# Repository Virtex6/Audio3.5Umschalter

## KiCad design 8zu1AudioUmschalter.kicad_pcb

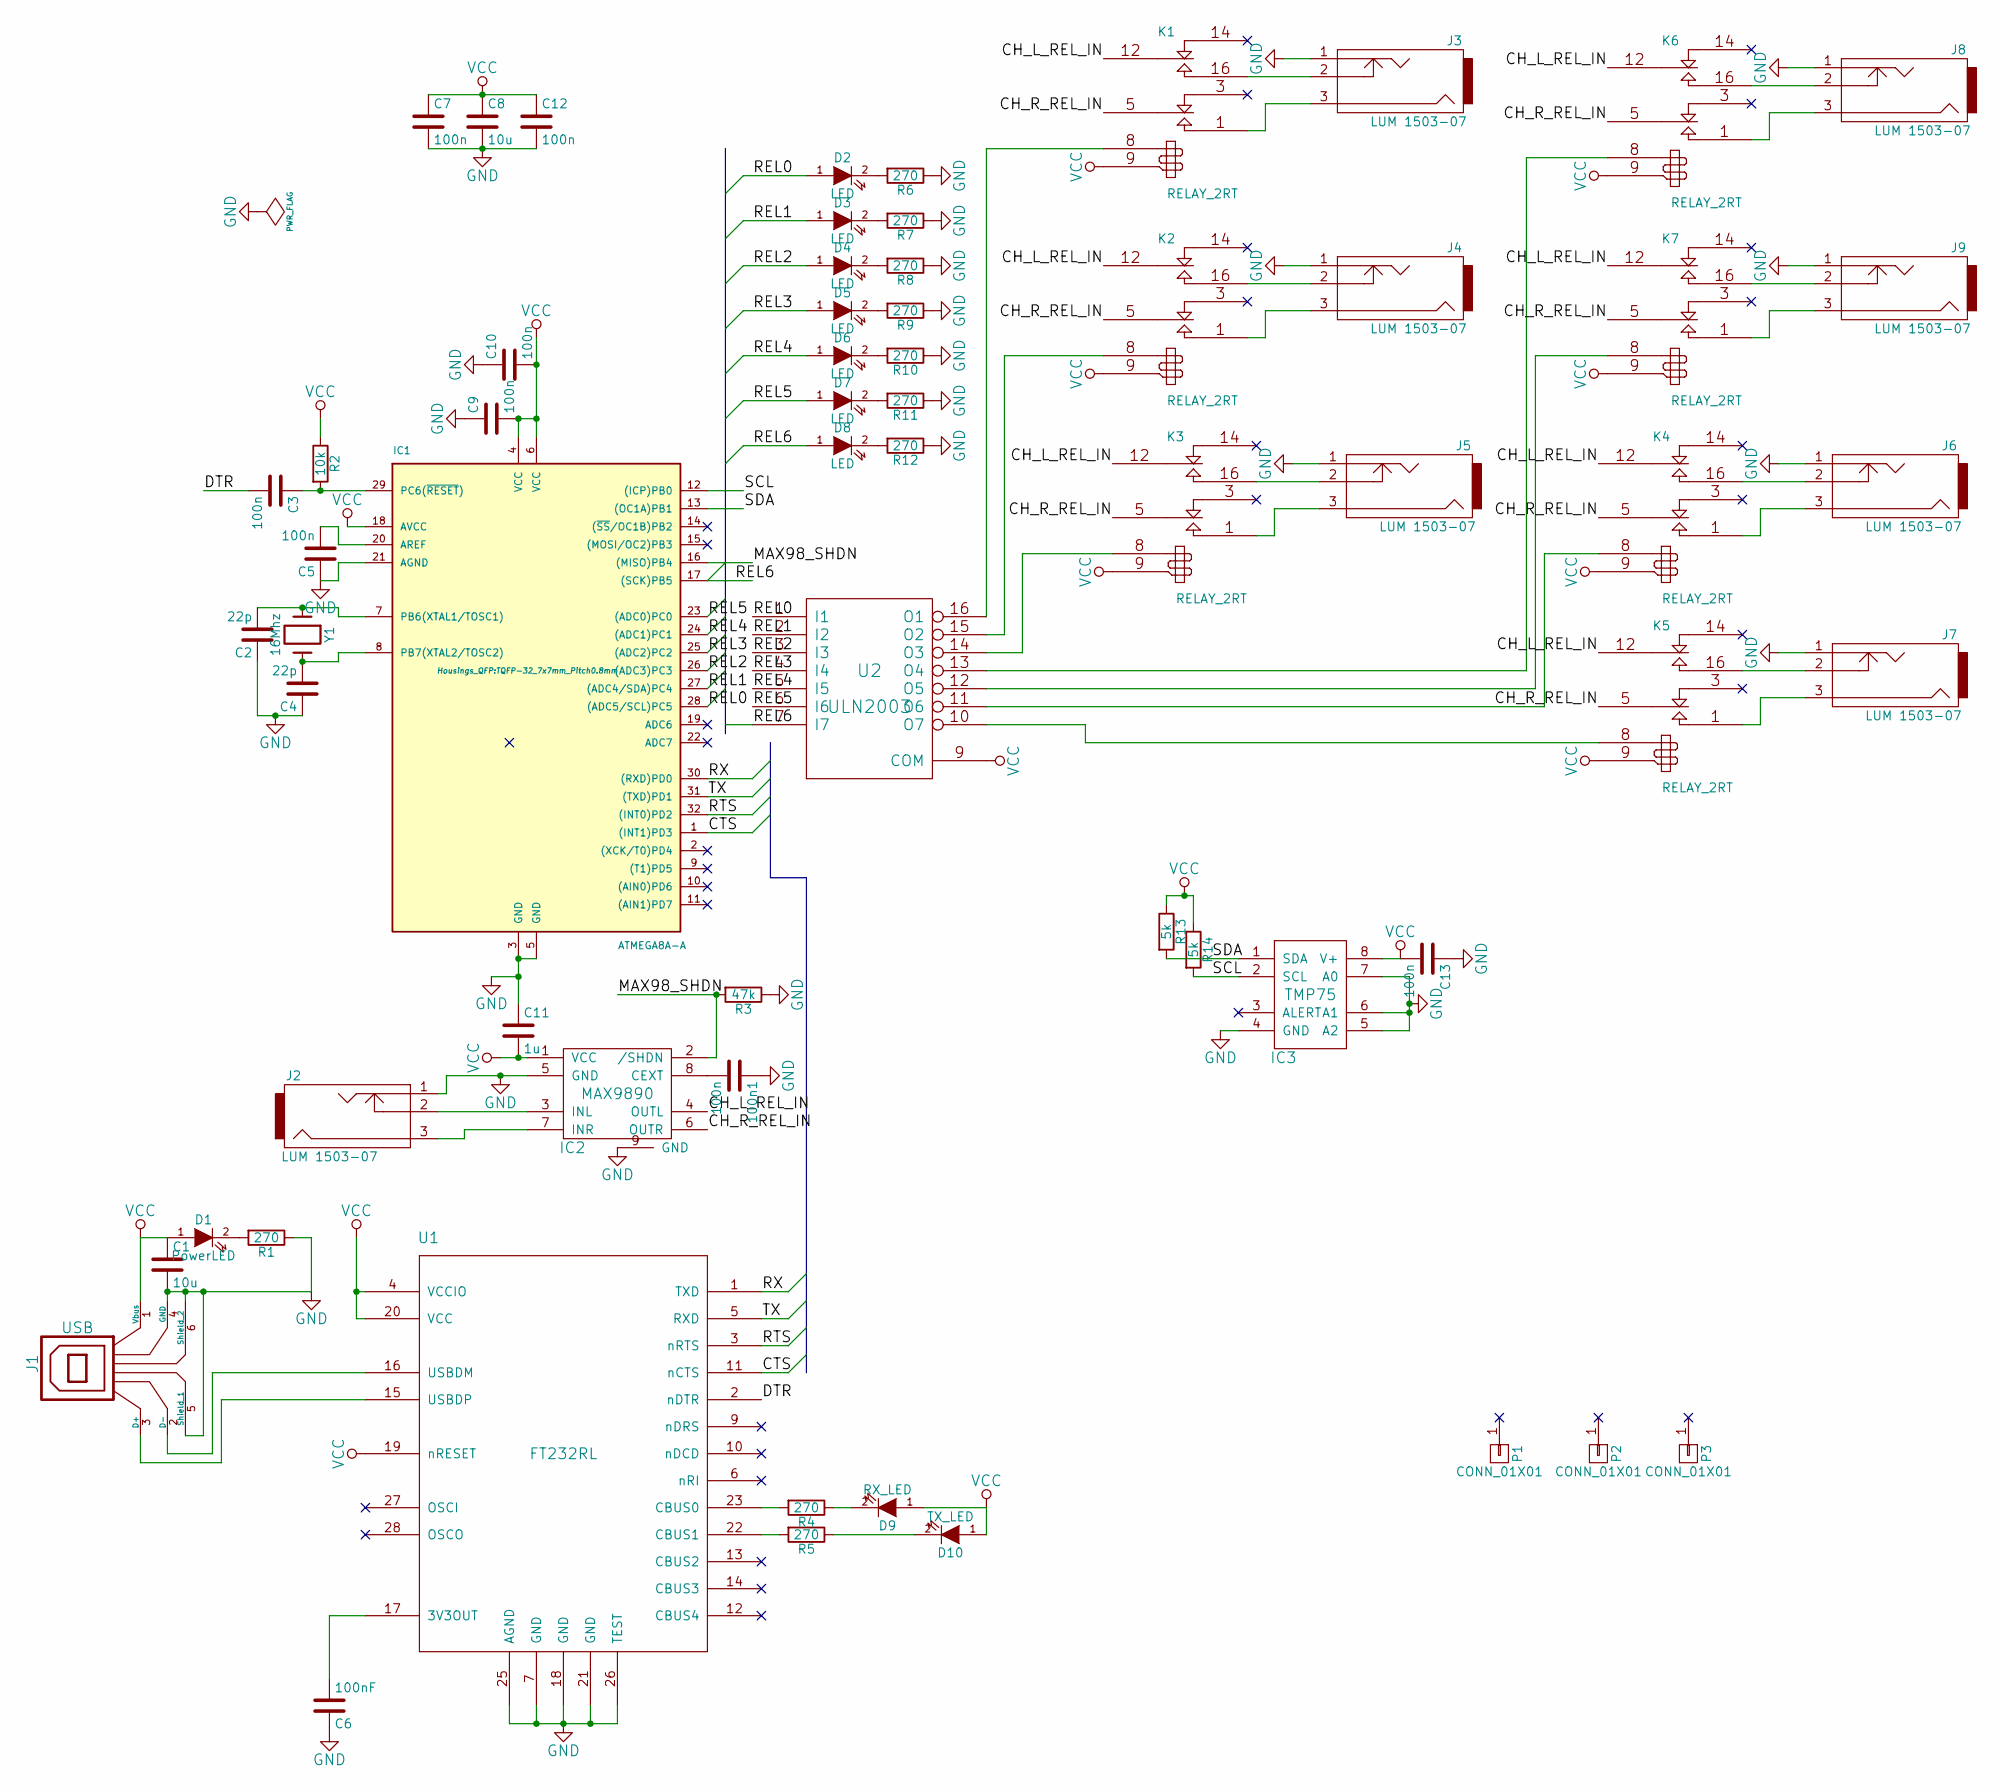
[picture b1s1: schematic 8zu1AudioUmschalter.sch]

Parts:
100n1: 100n; C_0603
C1, C8: 10u; C_0805
C2, C4: 22p; C_0603
C3, C5, C7, C9, C10, C12, C13: 100n; C_0603
C6: 100nF; C_0603
C11: 1u; C_0603
D1: PowerLED; LED-0603
D2, D3, D4, D5, D6, D7, D8: LED; LED-0603
D9: RX_LED; LED-0603
D10: TX_LED; LED-0603
IC1: ATMEGA8A-A; TQFP-32_7x7mm_Pitch0.8mm
IC2: MAX9890; DFN-8-1EP_3x3mm_Pitch0.65mm
IC3: TMP75; SOIC-8-N
J1: USB; USB_Mini-B
J2, J3, J4, J5, J6, J7, J8, J9: LUM 1503-07; LUM1503
K1, K2, K3, K4, K5, K6, K7: RELAY_2RT; REL_NA05W
P1, P2, P3: CONN_01X01; MountingHole_3mm
R1, R4, R5, R6, R7, R8, R9, R10, R11, R12: 270; R_0603
R2: 10k; R_0603
R3: 47k; R_0603
R13, R14: 5k; R_0603
U1: FT232RL; SSOP-28_5.3x10.2mm_Pitch0.65mm
U2: ULN2003; SO-16-N
Y1: 16Mhz; Crystal_HC49-U_Vertical

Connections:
/CH_L_REL_IN: IC2.4 (OUTL), K1.12 (C2), K2.12 (C2), K3.12 (C2), K4.12 (C2), K5.12 (C2), K6.12 (C2), K7.12 (C2)
/CH_R_REL_IN: IC2.6 (OUTR), K1.5 (C1), K2.5 (C1), K3.5 (C1), K4.5 (C1), K5.5 (C1), K6.5 (C1), K7.5 (C1)
/CTS: IC1.1 ((INT1)PD3), U1.11 (nCTS)
/DTR: C3.2, U1.2 (nDTR)
/MAX98_SHDN: IC1.16 ((MISO)PB4), IC2.2 (/SHDN), R3.2
/REL0: D2.1 (A), IC1.28 ((ADC5/SCL)PC5), U2.1 (I1)
/REL1: D3.1 (A), IC1.27 ((ADC4/SDA)PC4), U2.2 (I2)
/REL2: D4.1 (A), IC1.26 ((ADC3)PC3), U2.3 (I3)
/REL3: D5.1 (A), IC1.25 ((ADC2)PC2), U2.4 (I4)
/REL4: D6.1 (A), IC1.24 ((ADC1)PC1), U2.5 (I5)
/REL5: D7.1 (A), IC1.23 ((ADC0)PC0), U2.6 (I6)
/REL6: D8.1 (A), IC1.17 ((SCK)PB5), U2.7 (I7)
/RTS: IC1.32 ((INT0)PD2), U1.3 (nRTS)
/RX: IC1.30 ((RXD)PD0), U1.1 (TXD)
/SCL: IC1.12 ((ICP)PB0), IC3.2 (SCL), R14.2
/SDA: IC1.13 ((OC1A)PB1), IC3.1 (SDA), R13.2
/TX: IC1.31 ((TXD)PD1), U1.5 (RXD)
GND: 100n1.1, C1.2, C2.1, C4.1, C5.1, C6.1, C7.2, C8.2, C9.1, C10.1, C11.1, C12.2, C13.1, IC1.3 (GND), IC1.5 (GND), IC1.21 (AGND), IC2.5 (GND), IC2.9 (GND), IC3.4 (GND), IC3.5 (A2), IC3.6 (A1), IC3.7 (A0), J1.4 (GND), J1.5 (Shield_1), J1.6 (Shield_2), J2.1, J3.1, J4.1, J5.1, J6.1, J7.1, J8.1, J9.1, R1.1, R3.1, R6.1, R7.1, R8.1, R9.1, R10.1, R11.1, R12.1, U1.7 (GND), U1.18 (GND), U1.21 (GND), U1.25 (AGND), U1.26 (TEST), U2.8 (GND)
unnamed: 100n1.2, IC2.8 (CEXT)
unnamed: C2.2, IC1.7 (PB6(XTAL1/TOSC1)), Y1.1
unnamed: C3.1, IC1.29 (PC6(~RESET~)), R2.2
unnamed: C4.2, IC1.8 (PB7(XTAL2/TOSC2)), Y1.2
unnamed: C5.2, IC1.20 (AREF)
unnamed: C6.2, U1.17 (3V3OUT)
unnamed: D1.2 (K), R1.2
unnamed: D2.2 (K), R6.2
unnamed: D3.2 (K), R7.2
unnamed: D4.2 (K), R8.2
unnamed: D5.2 (K), R9.2
unnamed: D6.2 (K), R10.2
unnamed: D7.2 (K), R11.2
unnamed: D8.2 (K), R12.2
unnamed: D9.2 (K), R4.1
unnamed: D10.2 (K), R5.1
unnamed: IC2.3 (INL), J2.2
unnamed: IC2.7 (INR), J2.3
unnamed: J1.2 (D-), U1.16 (USBDM)
unnamed: J1.3 (D+), U1.15 (USBDP)
unnamed: J3.2, K1.16 (T2)
unnamed: J3.3, K1.1 (T1)
unnamed: J4.2, K2.16 (T2)
unnamed: J4.3, K2.1 (T1)
unnamed: J5.2, K3.16 (T2)
unnamed: J5.3, K3.1 (T1)
unnamed: J6.2, K4.16 (T2)
unnamed: J6.3, K4.1 (T1)
unnamed: J7.2, K5.16 (T2)
unnamed: J7.3, K5.1 (T1)
unnamed: J8.2, K6.16 (T2)
unnamed: J8.3, K6.1 (T1)
unnamed: J9.2, K7.16 (T2)
unnamed: J9.3, K7.1 (T1)
unnamed: K1.8, U2.16 (O1)
unnamed: K2.8, U2.15 (O2)
unnamed: K3.8, U2.14 (O3)
unnamed: K4.8, U2.11 (O6)
unnamed: K5.8, U2.10 (O7)
unnamed: K6.8, U2.13 (O4)
unnamed: K7.8, U2.12 (O5)
unnamed: R4.2, U1.23 (CBUS0)
unnamed: R5.2, U1.22 (CBUS1)
VCC: C1.1, C7.1, C8.1, C9.2, C10.2, C11.2, C12.1, C13.2, D1.1 (A), D9.1 (A), D10.1 (A), IC1.4 (VCC), IC1.6 (VCC), IC1.18 (AVCC), IC2.1 (VCC), IC3.8 (V+), J1.1 (Vbus), K1.9, K2.9, K3.9, K4.9, K5.9, K6.9, K7.9, R2.1, R13.1, R14.1, U1.4 (VCCIO), U1.19 (nRESET), U1.20 (VCC), U2.9 (COM)

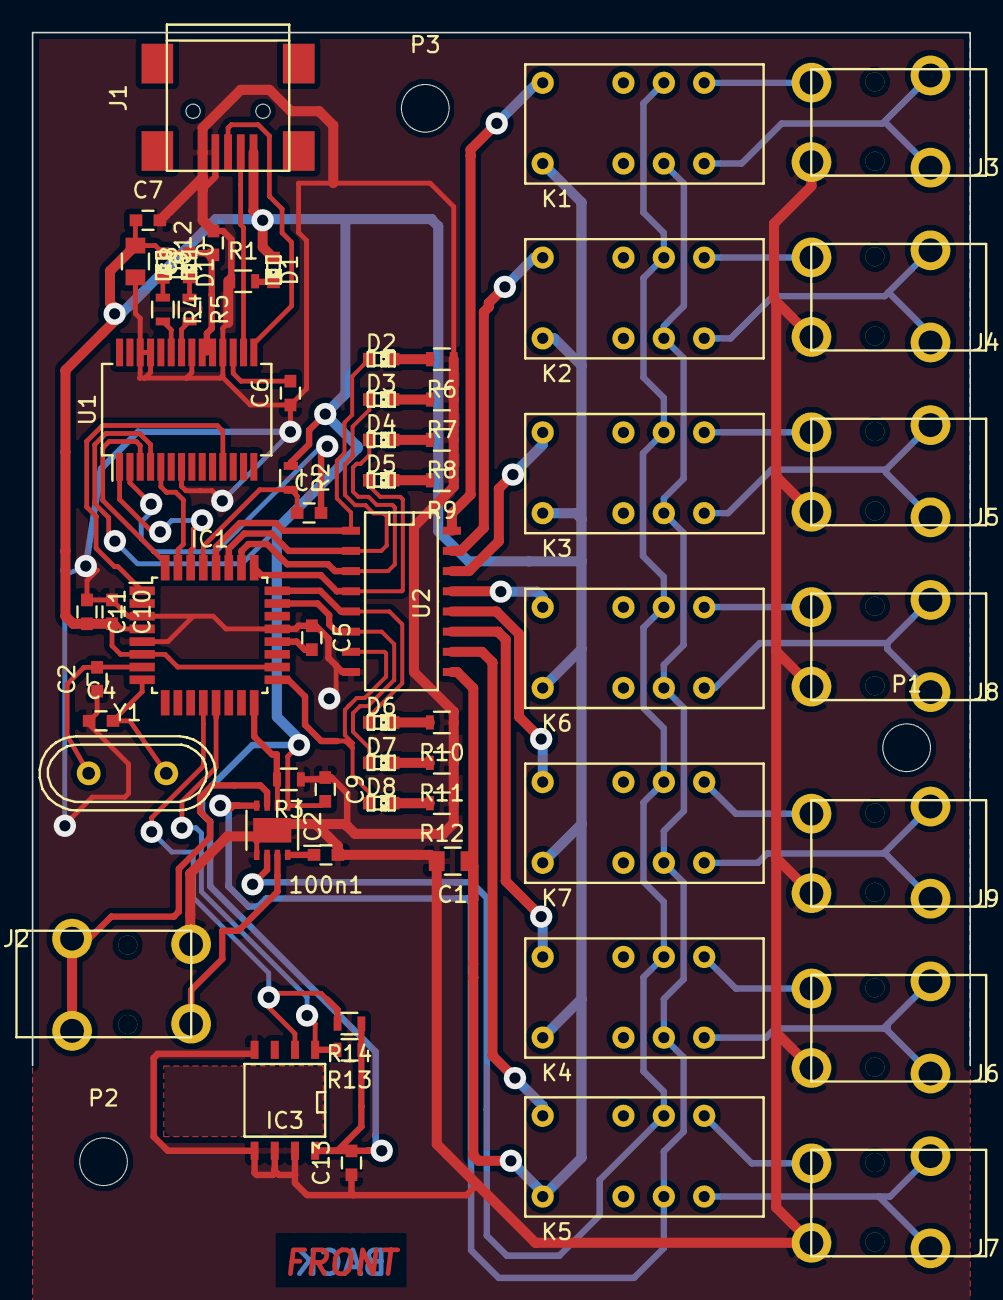
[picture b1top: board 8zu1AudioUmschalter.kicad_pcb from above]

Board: 2 copper layers, 59.0 x 65.0 mm, 63 parts (0 on the bottom side), 62 nets.

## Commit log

2015-03-15 Init commit
2015-03-15 DTR nun als RESET für den Atmega Entfernen des Konnektors für ISP
2015-03-15 Relays schalten nach low side (GND nach VCC geändert)
2015-03-15 Kleinere Anpassungen am MAX9890
2015-03-15 Hinzufügen von Status LEDs für die einzelnen Relais
2015-03-15 Pull Down am MAX9890 um Signal bewusst zu kontrollieren
2015-03-15 Hinzufügen der Libs
2015-03-15 Hinzufügen eines VCC stab. Kond. am MAX9890
2015-03-15 Kleinere Anpassungen
2015-03-16 Hinzufügen der Footprints und Datenblätter
2015-03-16 footprints für buchse und relais schauen ok aus, bauteile weiter zugeordnet
2015-03-16 Aktualisierung der Footprintzuordnung, Erstellen von TDFN8
2015-03-16 footprints für widerstände und maximchip angepasst
2015-03-16 Erster PCB Entwurf
2015-03-16 Erste vollständige PCB ohne Masseflächen
2015-03-16 Masseflächen dazu
2015-03-17 Platine nun 59 x 80 um den Abstand zwischen den 3.5 mm Buchsen zu vergrößern
2015-03-20 Kleinere Änderungen und Hinzufügen des TMP75
2015-03-20 Massefläche unter TMP75 entfernt
2015-03-21 Änderungen in den Masseflächen Ist es o.k. USB shield nicht mit GND zu verbinden ?
2015-03-21 Via Bohrdurchmesser angepasst
2015-03-21 Direkte Leiterbahnen zwischen Pads entfernt
2015-04-03 Text in Kupferlage dazugefügt, damit man richtig fertigen kann.
2015-04-03 Leitungen zu den Relais auf die Back Layer gelegt
2015-04-03 Layoutfehler, TX und RX waren nicht gekreuzt.
2015-04-05 Umpolen der Relais, da diese eine bestimmte Polarität benötigen
